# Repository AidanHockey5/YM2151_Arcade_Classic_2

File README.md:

https://www.youtube.com/watch?v=WZmMP82XPoI

# Arcade Classic 2

This project contains the source material for the Arcade Classic 2, a hybrid hardware/software YM2151 video game music (VGM) player. This device is based off of the [Mega Blaster 2 platform](https://github.com/AidanHockey5/MegaBlaster2) which was designed to play Sega Genesis/Megadrive VGM files.
This project utilizes a hybrid approach for rendering audio. All FM portions of the VGM file are played through a genuine YM2151 sound chip, while any extra soundchips, namely PCM soundchips, are pre-rendered and fed into an audio mixer circuit.
While it would be awesome to have genuine hardware support for every chip that was ever paired up with the YM2151, there are several factors that make that approach completely unfeasible. Namely, the vast amount of hardware configurations, memory requirements, sheer board space required, and rarity of components.
Therefore, this player is essentially playing back a WAV file for the external chips while also driving the genuine FM sound generator and mixing them together.
The result sounds pretty awesome!

# Special VGM File Requirements

The Arcade Classic 2 will read standard VGM/VGZ files just fine, however, in order to enable pre-rendered PCM support, you will need to quickly run your VGM files through a tool I've created. This tool will render out any portions of the VGM file that aren't controlling the YM2151 into a WAV file. The tool will then append the WAV data to the original VGM file. Finally, the tool will change the VGM header information so that the Arcade Classic 2 will recognize it as a PCM-compatible VGM file.

This tool is only compatible with Windows systems for now. It's fairly simple to use:

[Download the VGM_To_VGP Tool Here!!!](https://aidanlawrence.com/tools/ee/arcadeclassic2/vgm_to_vgp.zip)

1) Drag-and-drop VGM/VGZ files or folders containing VGM/VGZ onto the executable
2) Let the program render out each track
3) Add the newly created "VGP" files to your SD card!

Please note: WAV data is very bulky and will take up significantly more space than simple VGM/VGZ files.
This tool was written in C++ with Visual Studio 2017. It invokes [VGMPlay](https://github.com/vgmrips/vgmplay) to render the soundchip WAV data, then invokes [SoX](http://sox.sourceforge.net/) to ensure that the WAV data is in the correct format.
[The source code for VGM_To_VGP can be found here](https://github.com/AidanHockey5/YM2151_Arcade_Classic_2/tree/master/tools/vgmtovgp)

# VGM Files

VGM files are logged datasets of the data that would have been sent to the real sound chips of whatever console or arcade machine was being sampled. The Arcade Classic 2 simply reads-in this data and sends it to the sound chips at the exact rate specified in the VGM spec, accurately recreating the original sound.

You can find lots of VGM files here for all sorts of systems: https://vgmrips.net/packs/
The Arcade Classic 2 is only designed for soundtracks featuring the YM2151 sound chip. Technically, you could pre-render any VGM track you wanted and play it just fine, but that would essentially just be a WAV player with extra steps.

Please make sure to remove any non-vgm/vgz files before adding them to your Arcade Classic 2's SD card, such as album art images, playlist files, and text files.

# VGM vs. VGZ

VGZ files are gzip compressed versions of VGM files. The Arcade Classic 2 is capable of automatically decompressing these vgz files on-the-fly at a slight performance penalty. If you'd like faster load times for each track, consider decompressing the VGZ files in advance by opening them with a program like [7zip](https://www.7-zip.org/)
The Arcade Classic 2 does not require file extensions in order to operate as it will verify files based on their internal headers.

# Building Your Own Unit

Here are some quick tips for building your own board.

1) You can find an interactive Bill of Materials (BOM) within the `schematic->bom` folder. Open the HTML file in any browser for an easy-to-use part position guide.
2) I use [KiCAD](https://kicad.org/) as my EDA suite.
4) I buy most of my components from [LCSC](https://lcsc.com/). I buy my PCBs from [JLCPCB](https://jlcpcb.com/). If you buy your PCBs from JLCPCB, you can often get a shipping discount on your LCSC parts order.
5) You will need an [Atmel ICE](https://www.microchip.com/DevelopmentTools/ProductDetails/ATATMEL-ICE) or [Jlink](https://www.segger.com/products/debug-probes/j-link/) to flash the bootloader. Once you have flashed the bootloader, all subsequent programming can be done via the on-board USB port. A cheaper option would be to grab a [Jlink EDU Mini](https://shop-us.segger.com/J_Link_EDU_mini_p/8.08.91.htm) as they feature the full functionality of a professional Jlink Unit with the stipulation that it is ONLY to be used for educational purposes. I personally use an Atmel ICE unit. You can find the bootloader bin file in the `bootloader` folder of the repository. [You can find an example of me programming the bootloader using Microchip Studio here.](https://youtu.be/FjPftGuLnGg?t=9259)
This is the same bootloader that the Mega Blaster 2 uses, so the process is the same. You may notice that your Arcade Classic 2 is identified by your computer as a "Mega Blaster 2." This is fine.
7) Once you've flashed the bootloader, you can drag the [.uf2 firmware file found on the releases page](https://github.com/AidanHockey5/YM2151_Arcade_Classic_2/releases) on to the "drive" that pops up on your computer, or build from source. If you can't see any "drive," make sure the bootloader mentioned above is flashed correctly, then try double-tapping the RESET button. 
8) If your OS reports a USB fault, you may have a short somewhere on your USB IO lines, power lines, or your 32.768KHz crystal is not hooked up correctly.
9) If you'd like to modify the firmware, I use [Visual Studio Code](https://code.visualstudio.com/) with the [PlatformIO](https://platformio.org/install/ide?install=vscode) extension.

# Reporting Bugs

As you can imagine, this is quite a complex project. There are bound to be bugs to squish, so if you happen to find any, [please report them over on the issues page](https://github.com/AidanHockey5/YM2151_Arcade_Classic_2/issues) so I can tkae a look at them! Please try to document the steps it takes to recreate the bug if you happen to know them.

# Schematic

# License
The source code to this project is licensed under the AGPL 3.0 license.

The printed circuit board design files for the Arcade Classic 2, including it’s schematic, gerber files, KiCAD files, bill-of-materials, and 3D models are licensed under the Creative Commons Attribution-NonCommercial-ShareAlike 4.0 license.

You are permitted to build your own Arcade Classic 2 units for personal use. You are not permitted to sell said units.

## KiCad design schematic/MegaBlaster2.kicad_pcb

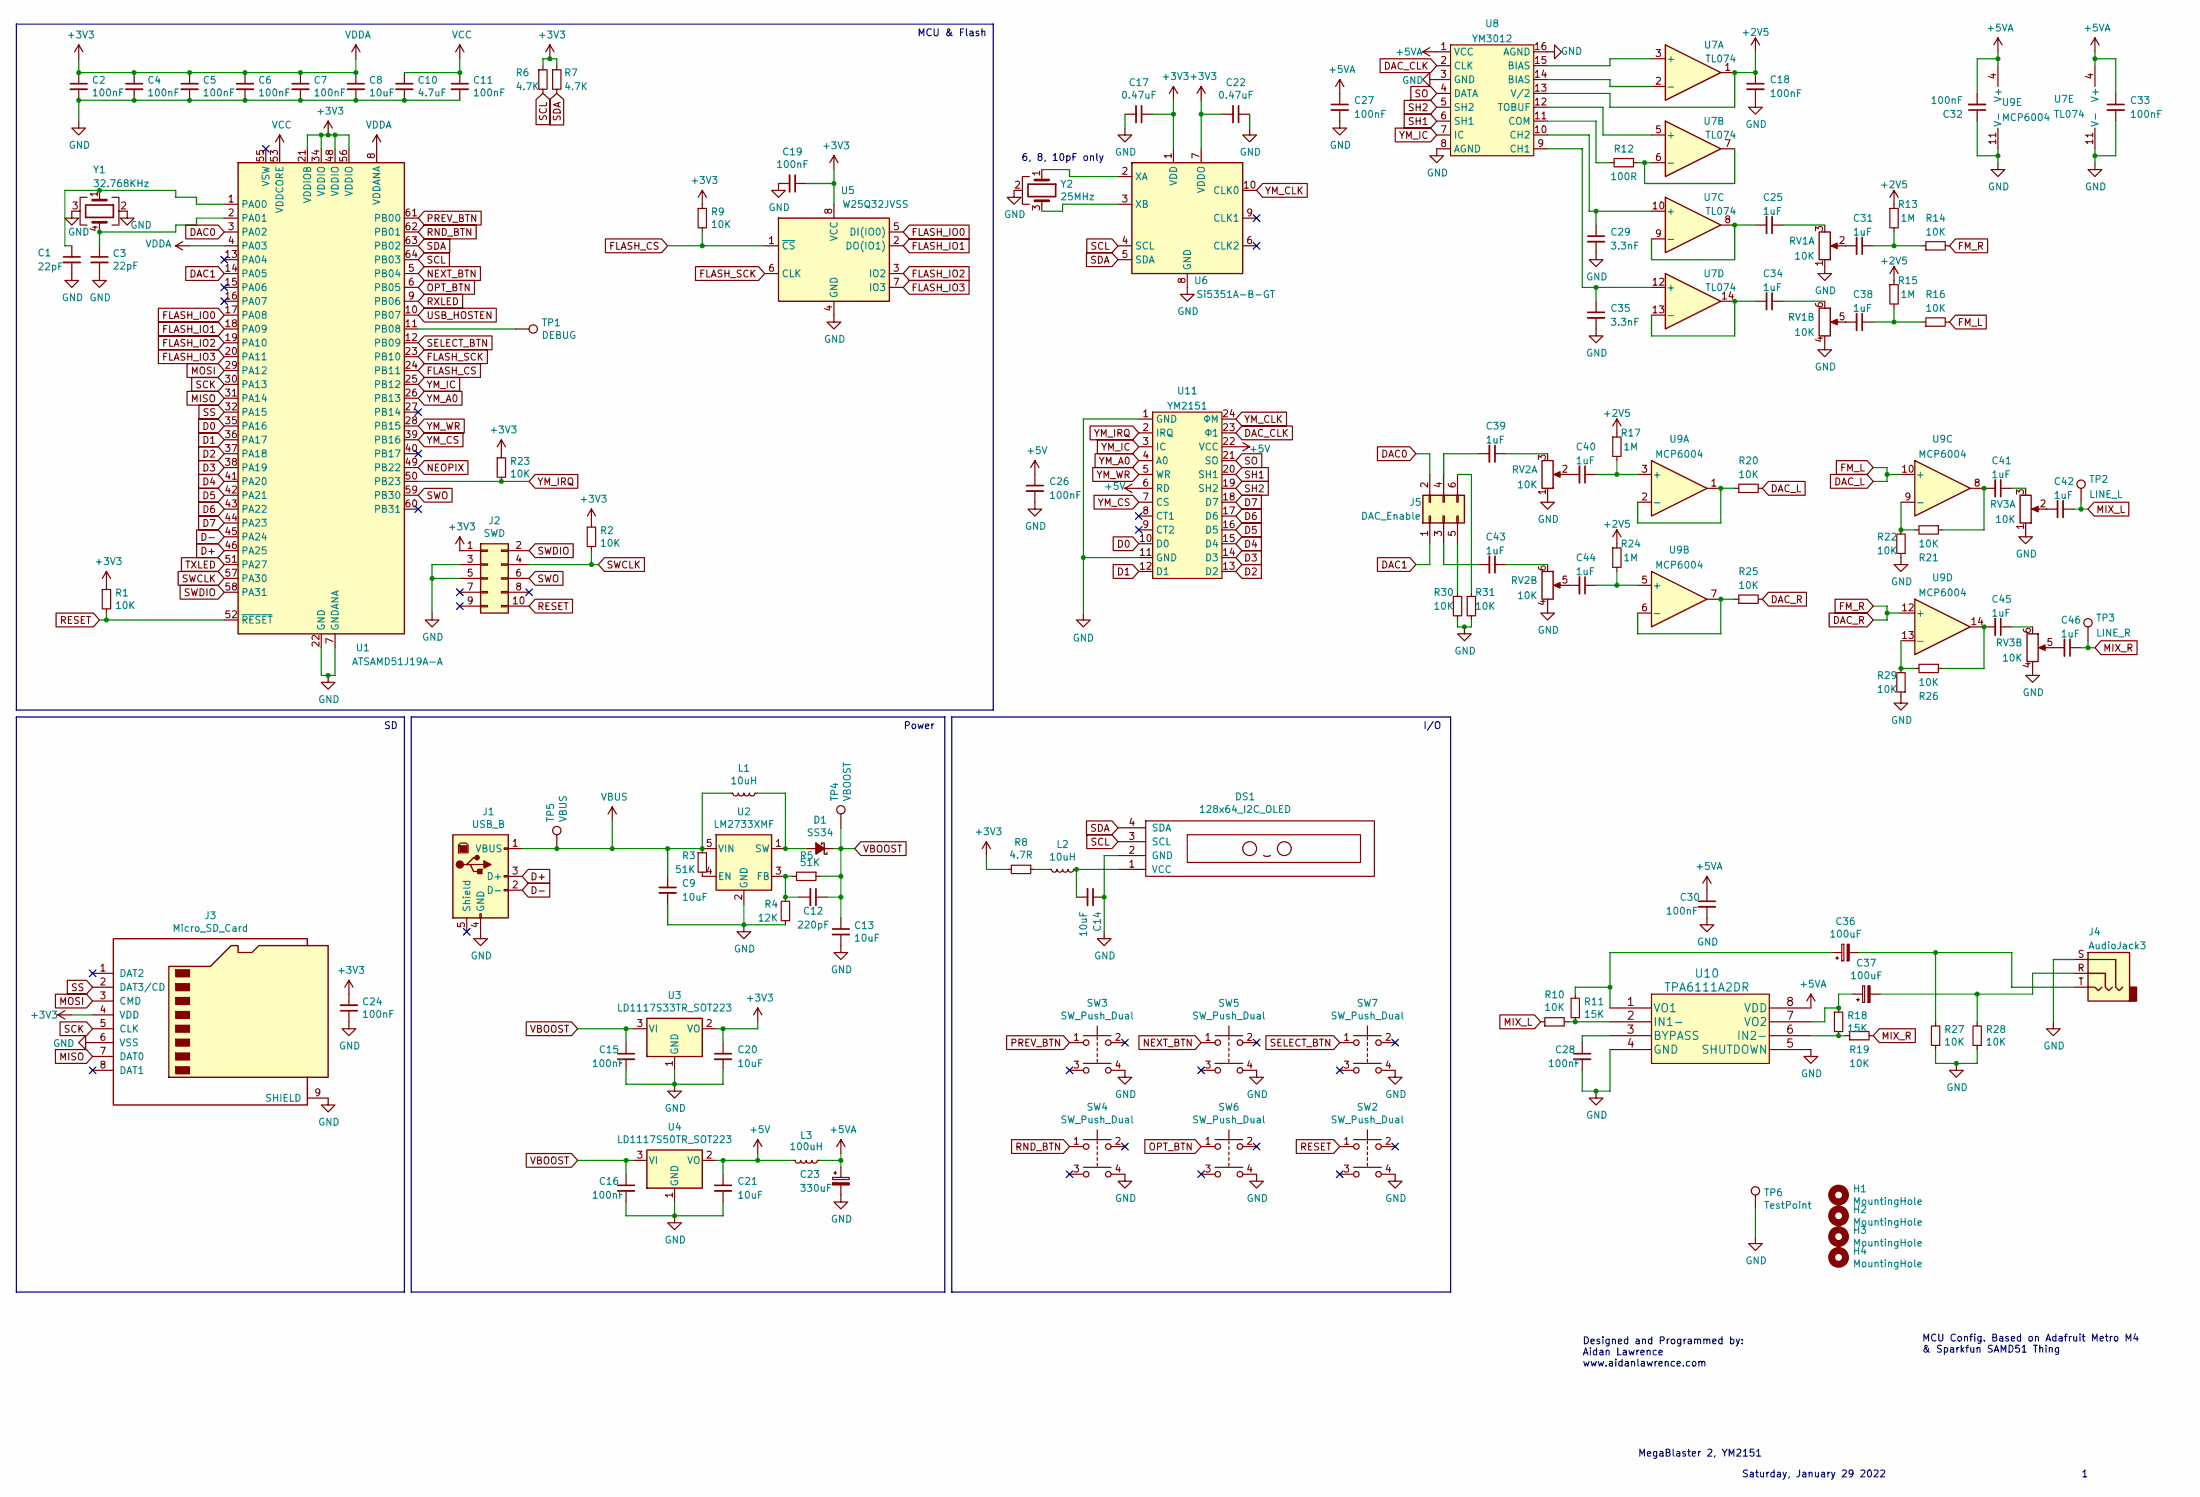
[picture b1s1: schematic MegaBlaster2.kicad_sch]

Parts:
C1, C3: 22pF; C_0603_1608Metric
C2, C4, C5, C6, C7, C11, C15, C16, C18, C19, C24, C26, C27, C28, C30, C32, C33: 100nF; C_0805_2012Metric
C8, C9, C13, C14, C20, C21: 10uF; C_1206_3216Metric
C10: 4.7uF; C_0805_2012Metric
C12: 220pF; C_0603_1608Metric
C17, C22: 0.47uF; C_0805_2012Metric
C23: 330uF; CP_Elec_8x10
C25, C31, C34, C38, C39, C40, C41, C42, C43, C44, C45, C46: 1uF; C_0805_2012Metric
C29, C35: 3.3nF; C_0805_2012Metric
C36, C37: 100uF; CP_Elec_6.3x7.7
D1: SS34; D_SMA
DS1: 128x64_I2C_OLED; oled_128x64
H1, H2, H3, H4: MountingHole; MountingHole_3.2mm_M3
J1: USB_B; USB_B_Lumberg_2411_02_Horizontal
J2: SWD; PinHeader_2x05_P1.27mm_Vertical
J3: Micro_SD_Card; SOFNG_TF_15x15_PUSH_PUSH
J4: AudioJack3; SWITCHCRAFT_35RAPC4BHN2
J5: DAC_Enable; PinHeader_2x03_P2.54mm_Vertical
L1, L2: 10uH; L_4x4
L3: 100uH; 6x6Inductor
R1, R2, R9, R10, R14, R16, R19, R20, R21, R22, R23, R25, R26, R27, R28, R29, R30, R31: 10K; R_0805_2012Metric
R3, R5: 51K; R_0805_2012Metric
R4: 12K; R_0805_2012Metric
R6, R7: 4.7K; R_0805_2012Metric
R8: 4.7R; R_0805_2012Metric
R11, R18: 15K; R_0805_2012Metric
R12: 100R; R_0805_2012Metric
R13, R15, R17, R24: 1M; R_0805_2012Metric
RV1, RV2, RV3: 10K; Potentiometer_Alps_RK097_Dual_Horizontal
SW2, SW3, SW4, SW5, SW6, SW7: SW_Push_Dual; SW_TH_Tactile_Omron_B3F-10xx
TP1: DEBUG; TestPoint_Pad_D2.0mm
TP2: LINE_L; TestPoint_Pad_D2.0mm
TP3: LINE_R; TestPoint_Pad_D2.0mm
TP4: VBOOST; TestPoint_Pad_D2.0mm
TP5: VBUS; TestPoint_Pad_D2.0mm
TP6: TestPoint; TestPoint_Pad_2.0x2.0mm
U1: ATSAMD51J19A-A; TQFP-64_10x10mm_P0.5mm
U2: LM2733XMF; SOT-23-5
U3: LD1117S33TR_SOT223; SOT-223-3_TabPin2
U4: LD1117S50TR_SOT223; SOT-223-3_TabPin2
U5: W25Q32JVSS; SOIC-8_5.23x5.23mm_P1.27mm
U6: Si5351A-B-GT; MSOP-10_3x3mm_P0.5mm
U7: TL074; SOIC-14_3.9x8.7mm_P1.27mm
U8: YM3012; DIP-16_W7.62mm_Socket
U9: MCP6004; SOIC-14_3.9x8.7mm_P1.27mm
U10: TPA6111A2DR; SOIC-8_3.9x4.9mm_P1.27mm
U11: YM2151; DIP-24_W15.24mm_Socket
Y1: 32.768KHz; Crystal_SMD_SeikoEpson_MC306-4Pin_8.0x3.2mm
Y2: 25MHz; Crystal_SMD_3225-4Pin_3.2x2.5mm

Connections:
+2V5: C18.1, R13.1, R15.1, R17.1, R24.1, U7.1, U8.13 (V/2)
+3V3: C2.1, C4.1, C5.1, C6.1, C7.1, C8.1, C17.1, C19.1, C20.1, C22.2, C24.2, J2.1, J3.4 (VDD), R1.1, R2.1, R6.1, R7.1, R8.2, R9.1, R23.1, U1.4 (PA03), U1.8 (VDDANA), U1.21 (VDDIOB), U1.34 (VDDIO), U1.48 (VDDIO), U1.56 (VDDIO), U3.2 (VO), U5.8 (VCC), U6.1 (VDD), U6.7 (VDDO)
+5V: C21.1, C26.1, L3.2, U4.2 (VO), U11.6 (RD), U11.22 (VCC)
+5VA: C23.1, C27.1, C30.1, C32.2, C33.1, L3.1, U7.4 (V+), U8.1 (VCC), U9.4 (V+), U10.8 (VDD)
D0: U1.35 (PA16), U11.10 (D0)
D1: U1.36 (PA17), U11.12 (D1)
D2: U1.37 (PA18), U11.13 (D2)
D3: U1.38 (PA19), U11.14 (D3)
D4: U1.41 (PA20), U11.15 (D4)
D5: U1.42 (PA21), U11.16 (D5)
D6: U1.43 (PA22), U11.17 (D6)
D7: U1.44 (PA23), U11.18 (D7)
D+: J1.3 (D+), U1.46 (PA25)
D-: J1.2 (D-), U1.45 (PA24)
DAC0: J5.2, U1.3 (PA02)
DAC1: J5.1, U1.14 (PA05)
DAC_CLK: U8.2 (CLK), U11.23 (Φ1)
DAC_L: R16.2, R20.2, U9.10 (+)
DAC_R: R14.2, R25.2, U9.12 (+)
FLASH_CS: R9.2, U1.24 (PB11), U5.1 (~CS)
FLASH_IO0: U1.17 (PA08), U5.5 (DI(IO0))
FLASH_IO1: U1.18 (PA09), U5.2 (DO(IO1))
FLASH_IO2: U1.19 (PA10), U5.3 (IO2)
FLASH_IO3: U1.20 (PA11), U5.7 (IO3)
FLASH_SCK: U1.23 (PB10), U5.6 (CLK)
GND: C1.2, C2.2, C3.2, C4.2, C5.2, C6.2, C7.2, C8.2, C9.2, C10.2, C11.2, C13.2, C14.1, C15.2, C16.2, C17.2, C18.2, C19.2, C20.2, C21.2, C22.1, C23.2, C24.1, C26.2, C27.2, C28.2, C29.2, C30.2, C32.1, C33.2, C35.2, DS1.2 (GND), J1.4 (GND), J2.3, J2.5, J3.6 (VSS), J3.9 (SHIELD), J4.S, R4.1, R22.1, R27.1, R28.1, R29.1, R30.2, R31.2, RV1.1 (6), RV1.4, RV2.1 (6), RV2.4, RV3.1 (6), RV3.4, SW2.4, SW3.4, SW4.4, SW5.4, SW6.4, SW7.4, TP6.1, U1.7 (GNDANA), U1.22 (GND), U1.33 (GND), U1.47 (GND), U1.54 (GND), U2.2 (GND), U3.1 (GND), U4.1 (GND), U5.4 (GND), U6.8 (GND), U7.11 (V-), U8.3 (GND), U8.8 (AGND), U8.16 (AGND), U9.11 (V-), U10.4 (GND), U10.5 (SHUTDOWN), U11.1 (GND), U11.11 (GND), Y1.2, Y1.3, Y2.2
MISO: J3.7 (DAT0), U1.31 (PA14)
MIX_L: C42.1, R10.1, TP2.1
MIX_R: C46.1, R19.2, TP3.1
MOSI: J3.3 (CMD), U1.29 (PA12)
NEOPIX: U1.49 (PB22)
NEXT_BTN: SW5.1, U1.5 (PB04)
unnamed: C1.1, U1.1 (PA00), Y1.1
unnamed: C3.1, U1.2 (PA01), Y1.4
unnamed: C12.2, R4.2, R5.2, U2.3 (FB)
unnamed: C14.2, DS1.1 (VCC), L2.1
unnamed: C25.1, RV1.3 (4)
unnamed: C25.2, U7.8, U7.9 (-)
unnamed: C28.1, U10.3 (BYPASS)
unnamed: C29.1, U7.10 (+), U8.10 (CH2)
unnamed: C31.1, R13.2, R14.1
unnamed: C31.2, RV1.2
unnamed: C34.1, RV1.6
unnamed: C34.2, U7.13 (-), U7.14
unnamed: C35.1, U7.12 (+), U8.9 (CH1)
unnamed: C36.1, R11.1, U10.1 (VO1)
unnamed: C36.2, J4.T, R27.2
unnamed: C37.1, R18.1, U10.7 (VO2)
unnamed: C37.2, J4.R, R28.2
unnamed: C38.1, R15.2, R16.1
unnamed: C38.2, RV1.5
unnamed: C39.1, RV2.3 (4)
unnamed: C39.2, J5.4
unnamed: C40.1, R17.2, U9.3 (+)
unnamed: C40.2, RV2.2
unnamed: C41.1, RV3.3 (4)
unnamed: C41.2, R21.1, U9.8
unnamed: C42.2, RV3.2
unnamed: C43.1, RV2.6
unnamed: C43.2, J5.3
unnamed: C44.1, R24.2, U9.5 (+)
unnamed: C44.2, RV2.5
unnamed: C45.1, RV3.6
unnamed: C45.2, R26.1, U9.14
unnamed: C46.2, RV3.5
unnamed: D1.2 (A), L1.1, U2.1 (SW)
unnamed: J5.5, R30.1
unnamed: J5.6, R31.1
unnamed: L2.2, R8.1
unnamed: R3.2, U2.4 (EN)
unnamed: R10.2, R11.2, U10.2 (IN1-)
unnamed: R18.2, R19.1, U10.6 (IN2-)
unnamed: R20.1, U9.1, U9.2 (-)
unnamed: R21.2, R22.2, U9.9 (-)
unnamed: R25.1, U9.6 (-), U9.7
unnamed: R26.2, R29.2, U9.13 (-)
unnamed: TP1.1, U1.11 (PB08)
unnamed: U6.2 (XA), Y2.1
unnamed: U6.3 (XB), Y2.3
unnamed: U7.2 (-), U8.14 (BIAS)
unnamed: U7.3 (+), U8.15 (BIAS)
unnamed: U7.5 (+), U8.12 (TOBUF)
unnamed: R12.1, U7.6 (-), U7.7
unnamed: R12.2, U8.11 (COM)
OPT_BTN: SW6.1, U1.6 (PB05)
PREV_BTN: SW3.1, U1.61 (PB00)
RESET: J2.10, R1.2, SW2.1, U1.52 (~RESET)
RND_BTN: SW4.1, U1.62 (PB01)
RXLED: U1.9 (PB06)
SCK: J3.5 (CLK), U1.30 (PA13)
SCL: DS1.3 (SCL), R6.2, U1.64 (PB03), U6.4 (SCL)
SDA: DS1.4 (SDA), R7.2, U1.63 (PB02), U6.5 (SDA)
SELECT_BTN: SW7.1, U1.12 (PB09)
SH1: U8.6 (SH1), U11.20 (SH1)
SH2: U8.5 (SH2), U11.19 (SH2)
SO: U8.4 (DATA), U11.21 (SO)
SS: J3.2 (DAT3/CD), U1.32 (PA15)
SWCLK: J2.4, R2.2, U1.57 (PA30)
SWDIO: J2.2, U1.58 (PA31)
SWO: J2.6, U1.59 (PB30)
TXLED: U1.51 (PA27)
USB_HOSTEN: U1.10 (PB07)
VBOOST: C12.1, C13.1, C15.1, C16.1, D1.1 (K), R5.1, TP4.1, U3.3 (VI), U4.3 (VI)
VBUS: C9.1, J1.1 (VBUS), L1.2, R3.1, TP5.1, U2.5 (VIN)
VCC: C10.1, C11.1, U1.53 (VDDCORE)
YM_A0: U1.26 (PB13), U11.4 (A0)
YM_CLK: U6.10 (CLK0), U11.24 (ΦM)
YM_CS: U1.39 (PB16), U11.7 (CS)
YM_IC: U1.25 (PB12), U8.7 (IC), U11.3 (IC)
YM_IRQ: R23.2, U1.50 (PB23), U11.2 (IRQ)
YM_WR: U1.28 (PB15), U11.5 (WR)

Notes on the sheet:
Power
MegaBlaster 2, YM2151
MCU & Flash
MCU Config. Based on Adafruit Metro M4 & Sparkfun SAMD51 Thing
I/O
6, 8, 10pF only
Saturday, January 29 2022
Designed and Programmed by: Aidan Lawrence www.aidanlawrence.com

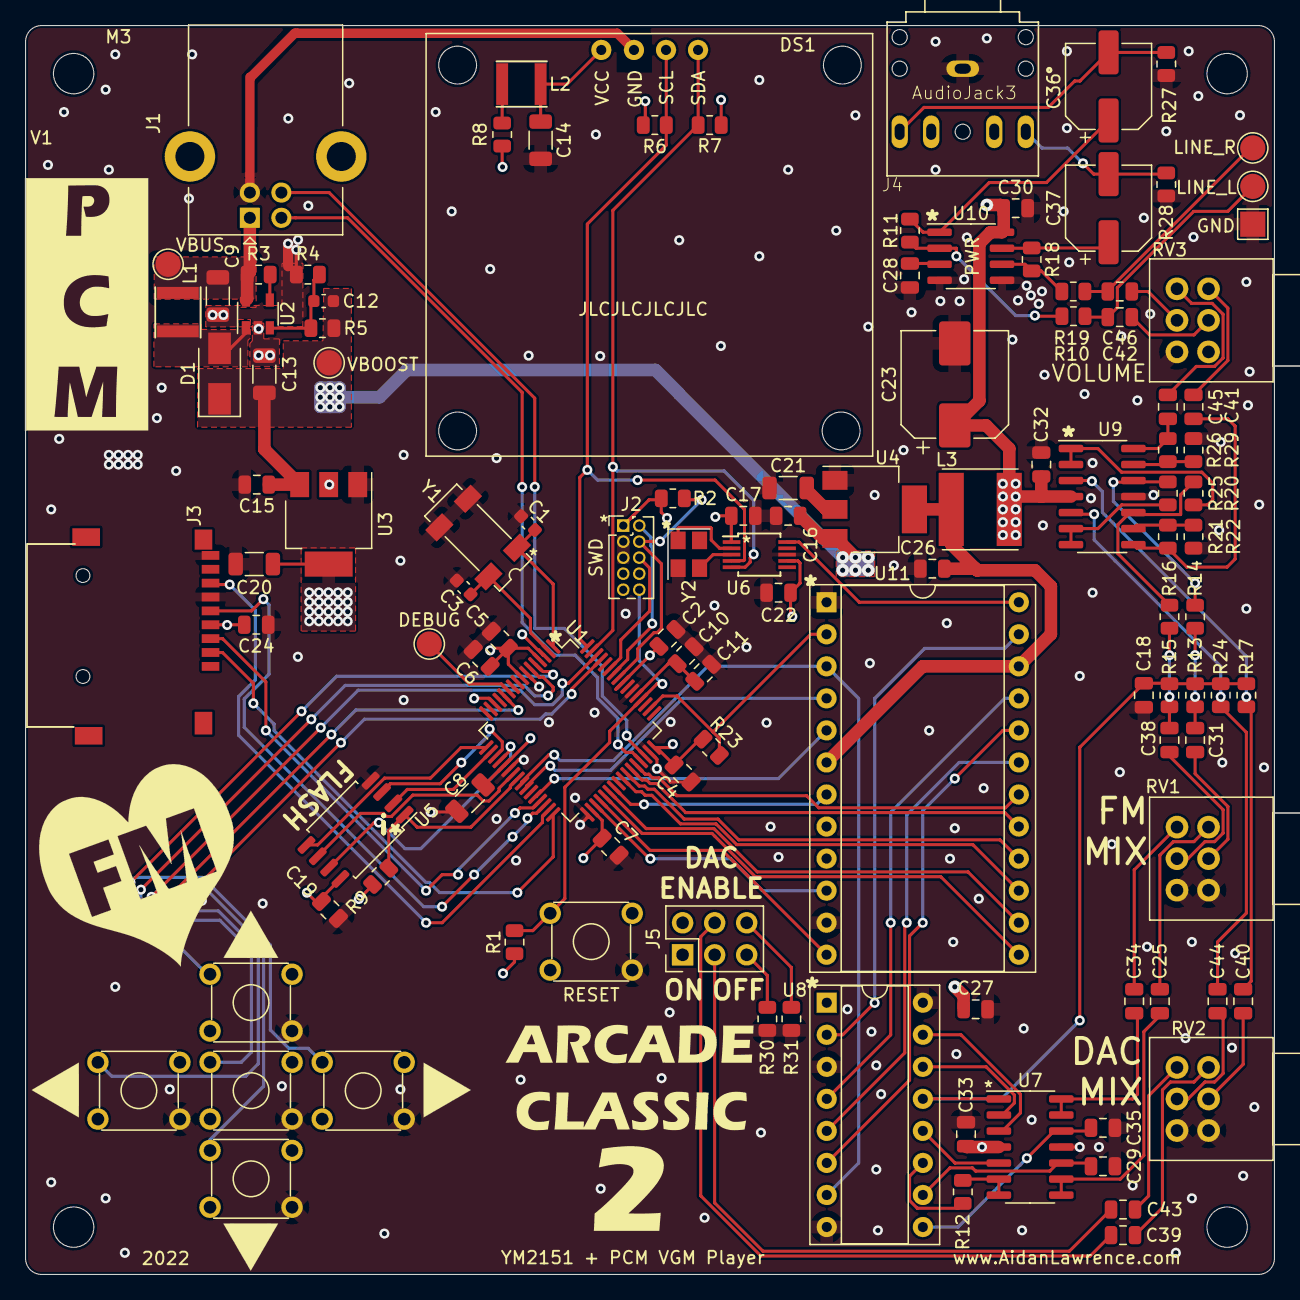
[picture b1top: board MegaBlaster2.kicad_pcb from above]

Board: 4 copper layers, 99.0 x 99.0 mm, 119 parts (0 on the bottom side), 107 nets.

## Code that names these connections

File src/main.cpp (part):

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bool isOledOn = true;

//Buttons
const int prev_btn = 47;    //PORT_PB00;
const int down_btn = 48;    //PORT_PB01;
const int next_btn = 49;    //PORT_PB04;
const int up_btn = 50;  //PORT_PB05;
const int select_btn = 19;  //PORT_PB09;
Bounce buttons[5];

//Counters
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  u8g2.clearDisplay();

  //SD
  REG_PORT_DIRSET0 = PORT_PA15; //Set PA15 to output
  if(!SD.begin(PORT_PA15, SPI_FULL_SPEED))
  {
    Serial.println("SD Mount Failed!");
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  //Direct IO examples for reading pins
  //if (REG_PORT_IN0 & PORT_PA19)  // if (digitalRead(12) == HIGH)
  //if (!(REG_PORT_IN0 | ~PORT_PA19)) // if (digitalRead(12) == LOW) FOR NON-PULLED PINS!
  //if(!(REG_PORT_IN1 & next_btn)) //LOW for PULLED PINS

  // //Group 1 is port B, PINCFG just wants the literal pin number on the port, DIRCLR and OUTSET want the masked PORT_XX00 *not* the PIN_XX00
  // //Prev button input pullup
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
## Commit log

2022-01-09 init
2022-01-09 moding mb2 to support ym2151
2022-01-09 timing and PCM skip prototyping
2022-01-09 pcm prototype save
2022-01-10 save
2022-01-10 Fixed WAV loop issue. No more head exploding white noise
2022-01-16 pcm skip
2022-01-16 fixed pcm load crash on non-looping tracks
2022-01-30 schematic v1
2022-01-30 footprints
2022-01-30 remove old traces and devices
2022-01-31 PCB first pass
2022-02-01 PCB v1
2022-02-03 Stop ISR on nav event to prevent crash
2022-02-25 2M resistor update
2022-03-11 temp watchdog to prevent ear destruction
2022-06-09 save before schm. rename
2022-06-09 rename schematic
2022-06-09 Add vgmtovgp source
